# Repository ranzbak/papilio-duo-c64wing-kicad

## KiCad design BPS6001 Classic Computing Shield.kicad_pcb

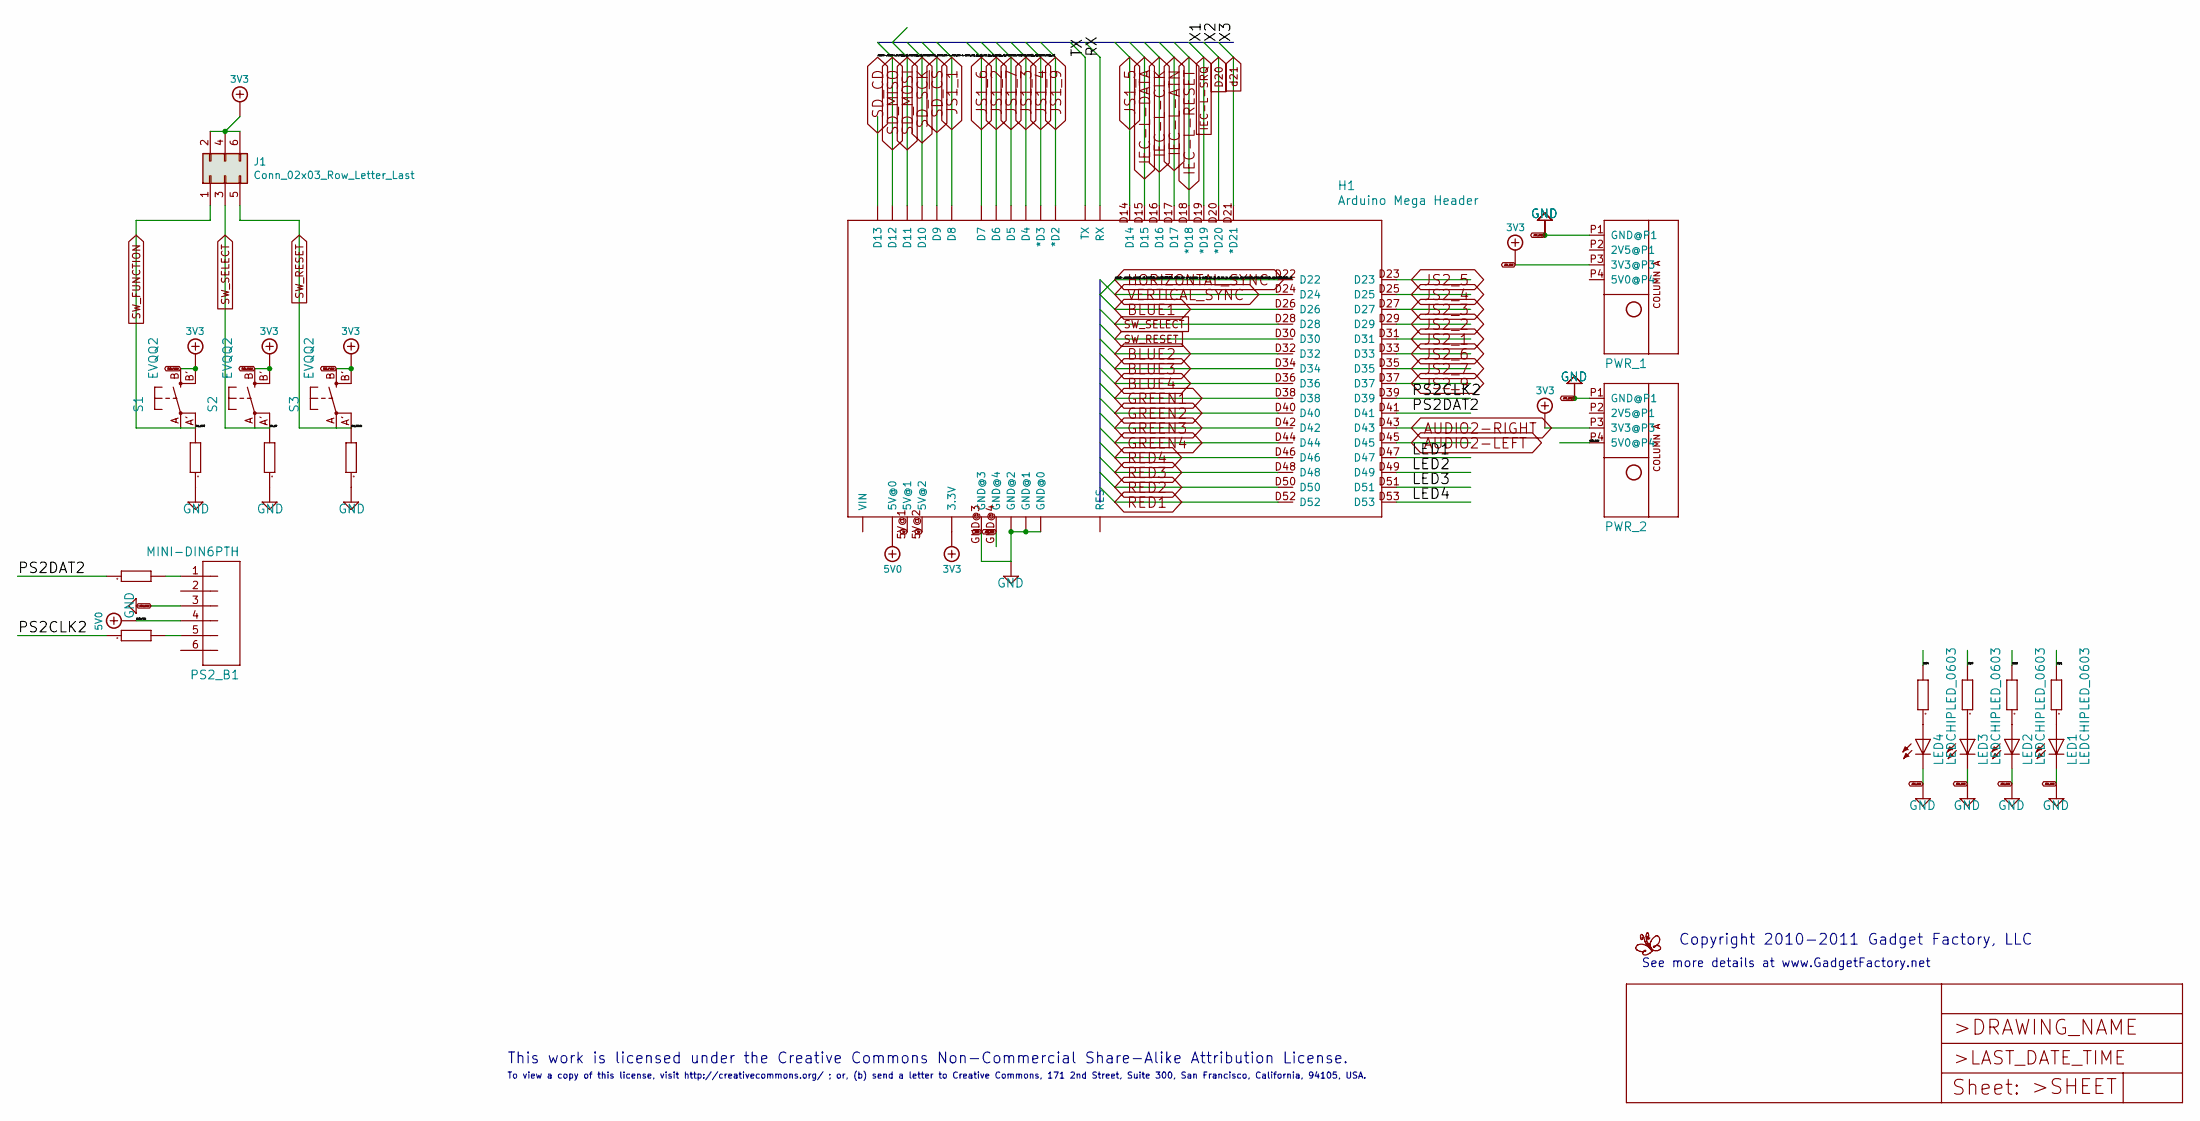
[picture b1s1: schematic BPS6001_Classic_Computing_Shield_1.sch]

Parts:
H1: Arduino Mega Header; AMEGA_SHIELD_NOANALOG; PARTNO Arduino_Mega_Header
J1: Conn_02x03_Row_Letter_Last; PinSocket_2x03_P2.54mm_Vertical
LED1, LED2, LED3, LED4: LEDCHIPLED_0603; CHIPLED_0603; PARTNO LTST-C190GKT
LOGO1: BUTTERFLY_LOGO
PS2_B: MINI-DIN6PTH; MINI-DIN6
PWR_1, PWR_2: POWER_ONLYNOTEXT; POWER_NO_TEXT
R9, R10, R17: 47K; 0603; PARTNO RMCF0603JT47K0
R26, R27, R43, R44, R47, R48: 390; 0603; PARTNO RMCF0603JT390R
S1, S3, S4: EVQQ2; EVQ-Q2; PARTNO PTS525SM10SMTR LFS

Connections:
3V3_PWR6: H1.3.3V, J1.2, J1.4, J1.6, PWR_1.P3 (3V3@P3), PWR_2.P3 (3V3@P3), S1.B (S), S1.B' (S1), S3.B (S), S3.B' (S1); also elsewhere on the board
5V: H1.5V@1, H1.5V@2
5V0: H1.5V@0, PWR_2.P4 (5V0@P4); also elsewhere on the board
/BPS6001 Classic Computing Shield_1/LED1: H1.D47, R26.2
/BPS6001 Classic Computing Shield_1/LED2: H1.D49, R27.2
/BPS6001 Classic Computing Shield_1/LED3: H1.D51, R43.2
/BPS6001 Classic Computing Shield_1/LED4: H1.D53, R44.2
/BPS6001 Classic Computing Shield_1/PS2CLK2: H1.D39, R48.1
/BPS6001 Classic Computing Shield_1/PS2DAT2: H1.D41, R47.1
/BPS6001 Classic Computing Shield_1/RX: H1.RX
/BPS6001 Classic Computing Shield_1/TX: H1.TX
AUDIO2-LEFT: H1.D45; also elsewhere on the board
AUDIO2-RIGHT: H1.D43; also elsewhere on the board
BLUE1: H1.D26; also elsewhere on the board
BLUE2: H1.D32; also elsewhere on the board
BLUE3: H1.D34; also elsewhere on the board
BLUE4: H1.D36; also elsewhere on the board
GND: H1.GND@0, H1.GND@1, H1.GND@2, H1.GND@3, H1.GND@4, LED1.C, LED2.C, LED3.C, LED4.C, PWR_1.P1 (GND@P1), PWR_2.P1 (GND@P1), R9.1, R10.1, R17.1; also elsewhere on the board
GREEN1: H1.D38; also elsewhere on the board
GREEN2: H1.D40; also elsewhere on the board
GREEN3: H1.D42; also elsewhere on the board
GREEN4: H1.D44; also elsewhere on the board
HORIZONTAL_SYNC: H1.D22; also elsewhere on the board
IEC-L-ATN: H1.D17; also elsewhere on the board
IEC-L-CLK: H1.D16; also elsewhere on the board
IEC-L-DATA: H1.D15; also elsewhere on the board
IEC-L-RESET: H1.D18 (*D18); also elsewhere on the board
IEC-L-SRQ: H1.D19 (*D19); also elsewhere on the board
JS1_1: H1.D8; also elsewhere on the board
JS1_2: H1.D6; also elsewhere on the board
JS1_3: H1.D4; also elsewhere on the board
JS1_4: H1.D3 (*D3); also elsewhere on the board
JS1_5: H1.D14; also elsewhere on the board
JS1_6: H1.D7; also elsewhere on the board
JS1_7: H1.D5; also elsewhere on the board
JS1_9: H1.D2 (*D2); also elsewhere on the board
JS2_1: H1.D31; also elsewhere on the board
JS2_2: H1.D29; also elsewhere on the board
JS2_3: H1.D27; also elsewhere on the board
JS2_4: H1.D25; also elsewhere on the board
JS2_5: H1.D23; also elsewhere on the board
JS2_6: H1.D33; also elsewhere on the board
JS2_7: H1.D35; also elsewhere on the board
JS2_9: H1.D37; also elsewhere on the board
unnamed: LED1.A, R26.1
unnamed: LED2.A, R27.1
unnamed: LED3.A, R43.1
unnamed: LED4.A, R44.1
unnamed 63: R47.2; also elsewhere on the board
unnamed 65: R48.2; also elsewhere on the board
RED1: H1.D52; also elsewhere on the board
RED2: H1.D50; also elsewhere on the board
RED3: H1.D48; also elsewhere on the board
RED4: H1.D46; also elsewhere on the board
SD_MISO: H1.D12; also elsewhere on the board
SD_MOSI: H1.D11; also elsewhere on the board
SD_SCK: H1.D10; also elsewhere on the board
SD_~CS: H1.D9; also elsewhere on the board
VERTICAL_SYNC: H1.D24; also elsewhere on the board

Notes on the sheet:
This work is licensed under the Creative Commons Non-Commercial Share-Alike Attribution License.
To view a copy of this license, visit http://creativecommons.org/ ; or, (b) send a letter to Creative Commons, 171 2nd Street, Suite 300, San Francisco, California, 94105, USA.
Copyright 2010-2011 Gadget Factory, LLC
See more details at www.GadgetFactory.net

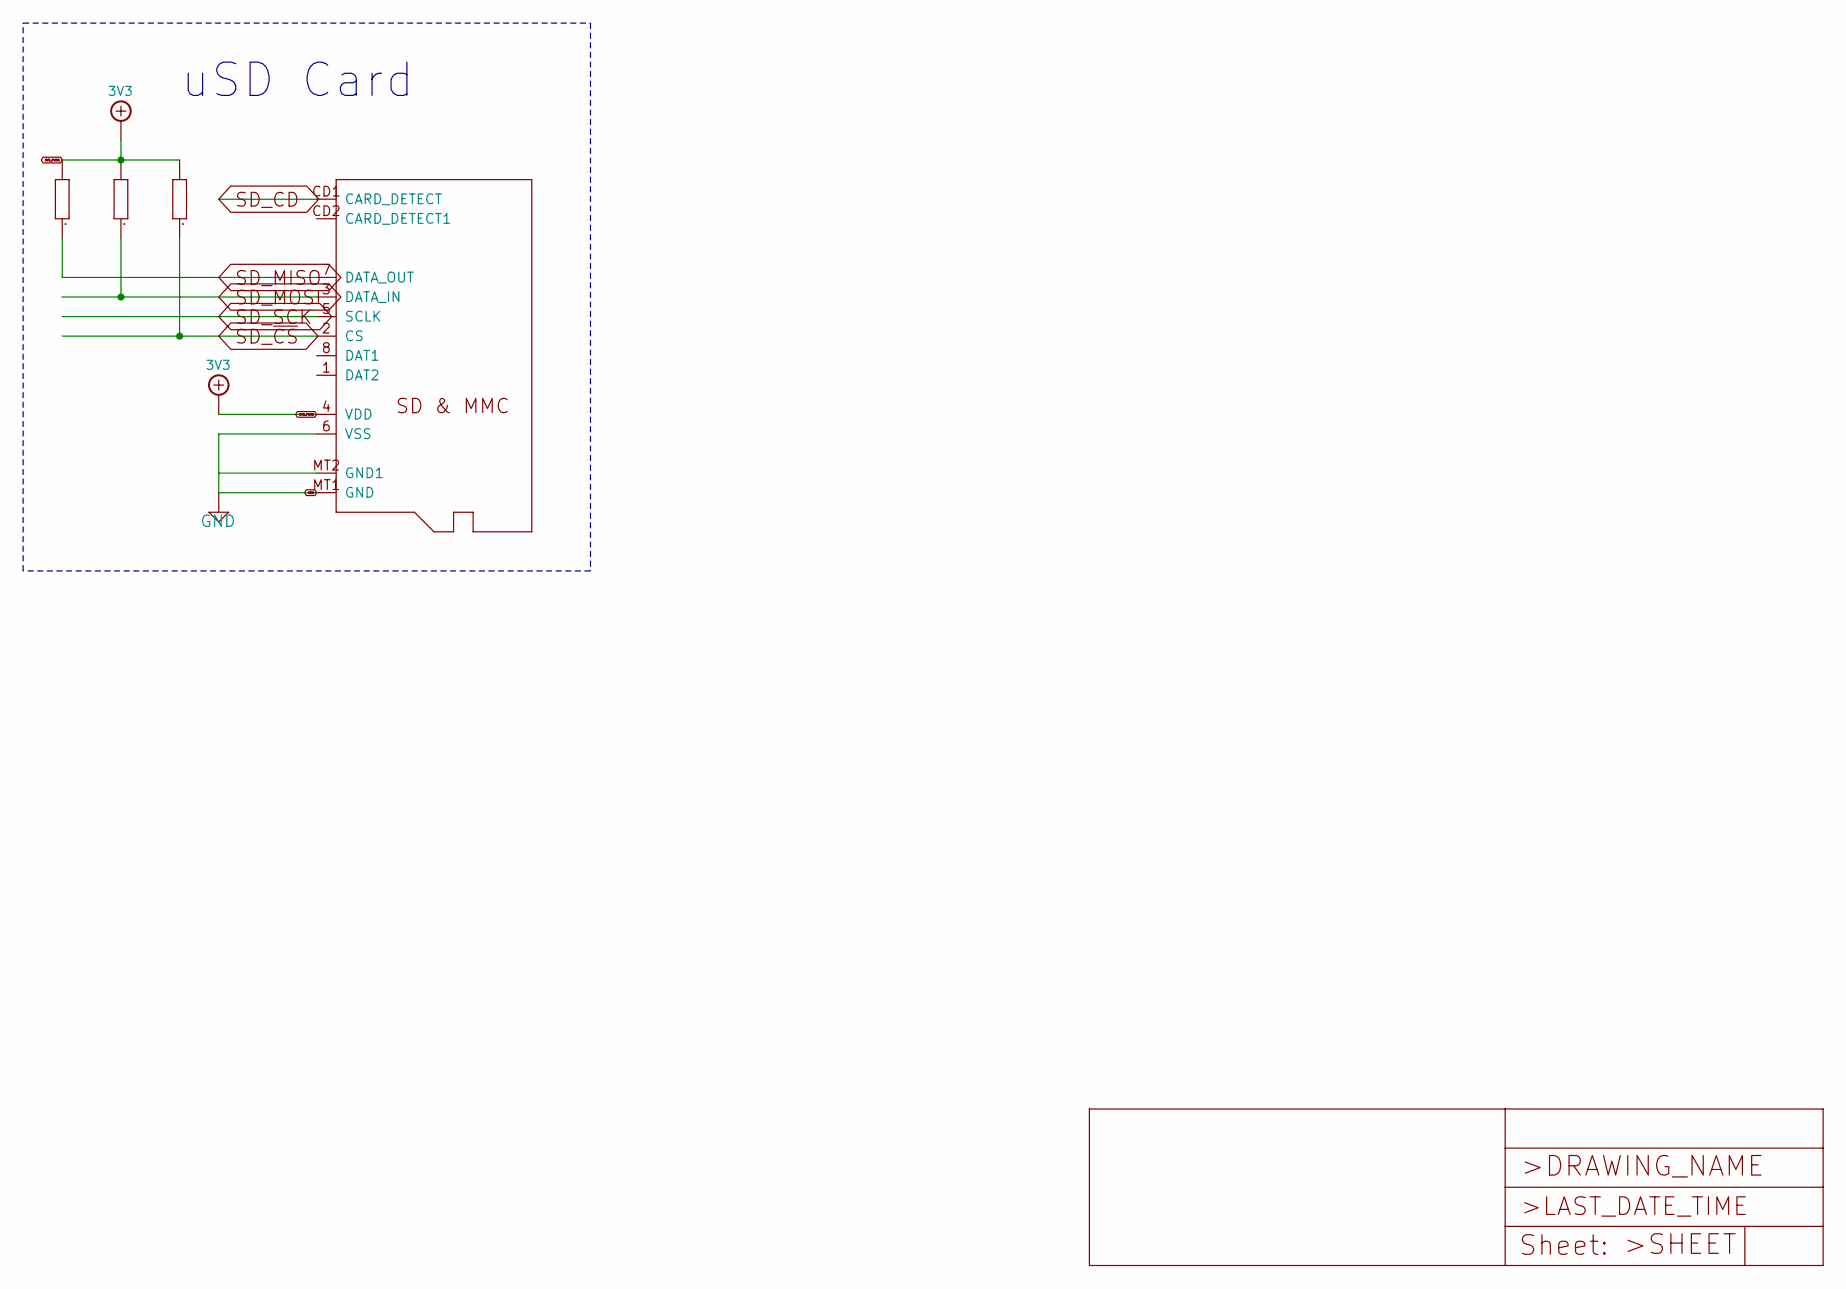
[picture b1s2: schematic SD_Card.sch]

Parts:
R23, R24, R25: 47K; 0603; PARTNO RMCF0603JT47K0
SD1: MICROSD; PARTNO 101-00660-68-6

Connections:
3V3_PWR6: R23.2, R24.2, R25.2, SD1.4 (VDD); also elsewhere on the board
GND: SD1.6 (VSS), SD1.MT1 (GND), SD1.MT2 (GND1); also elsewhere on the board
SD_CD: SD1.CD1 (CARD_DETECT)
SD_MISO: R23.1, SD1.7 (DATA_OUT); also elsewhere on the board
SD_MOSI: R24.1, SD1.3 (DATA_IN); also elsewhere on the board
SD_SCK: SD1.5 (SCLK); also elsewhere on the board
SD_~CS: R25.1, SD1.2 (CS); also elsewhere on the board

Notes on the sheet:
uSD Card

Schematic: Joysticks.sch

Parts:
JS1, JS2: Serial Port; M09HP; PARTNO 10090097-P094VLF
R1, R2, R3, R4, R5, R6, R7, R8, R12, R13, R14, R15, R16, R19, R20, R21: 47K; 0603; PARTNO RMCF0603JT47K0

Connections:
3V3_PWR6: R1.2, R2.2, R3.2, R4.2, R5.2, R6.2, R7.2, R8.2, R12.2, R13.2, R14.2, R15.2, R16.2, R19.2, R20.2, R21.2; also elsewhere on the board
GND: JS1.8, JS2.8; also elsewhere on the board
JS1_1: JS1.1, R1.1; also elsewhere on the board
JS1_2: JS1.2, R3.1; also elsewhere on the board
JS1_3: JS1.3, R5.1; also elsewhere on the board
JS1_4: JS1.4, R6.1; also elsewhere on the board
JS1_5: JS1.5, R8.1; also elsewhere on the board
JS1_6: JS1.6, R2.1; also elsewhere on the board
JS1_7: JS1.7, R4.1; also elsewhere on the board
JS1_9: JS1.9, R7.1; also elsewhere on the board
JS2_1: JS2.1, R16.1; also elsewhere on the board
JS2_2: JS2.2, R15.1; also elsewhere on the board
JS2_3: JS2.3, R14.1; also elsewhere on the board
JS2_4: JS2.4, R13.1; also elsewhere on the board
JS2_5: JS2.5, R12.1; also elsewhere on the board
JS2_6: JS2.6, R19.1; also elsewhere on the board
JS2_7: JS2.7, R20.1; also elsewhere on the board
JS2_9: JS2.9, R21.1; also elsewhere on the board

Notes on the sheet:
This work is licensed under the Creative Commons Non-Commercial Attribution Share-Alike License.
To view a copy of this license, visit http://creativecommons.org/ ; or, (b) send a letter to Creative Commons, 171 2nd Street, Suite 300, San Francisco, California, 94105, USA.
Copyright 2010-2012 Gadget Factory, LLC
See more details at www.GadgetFactory.net

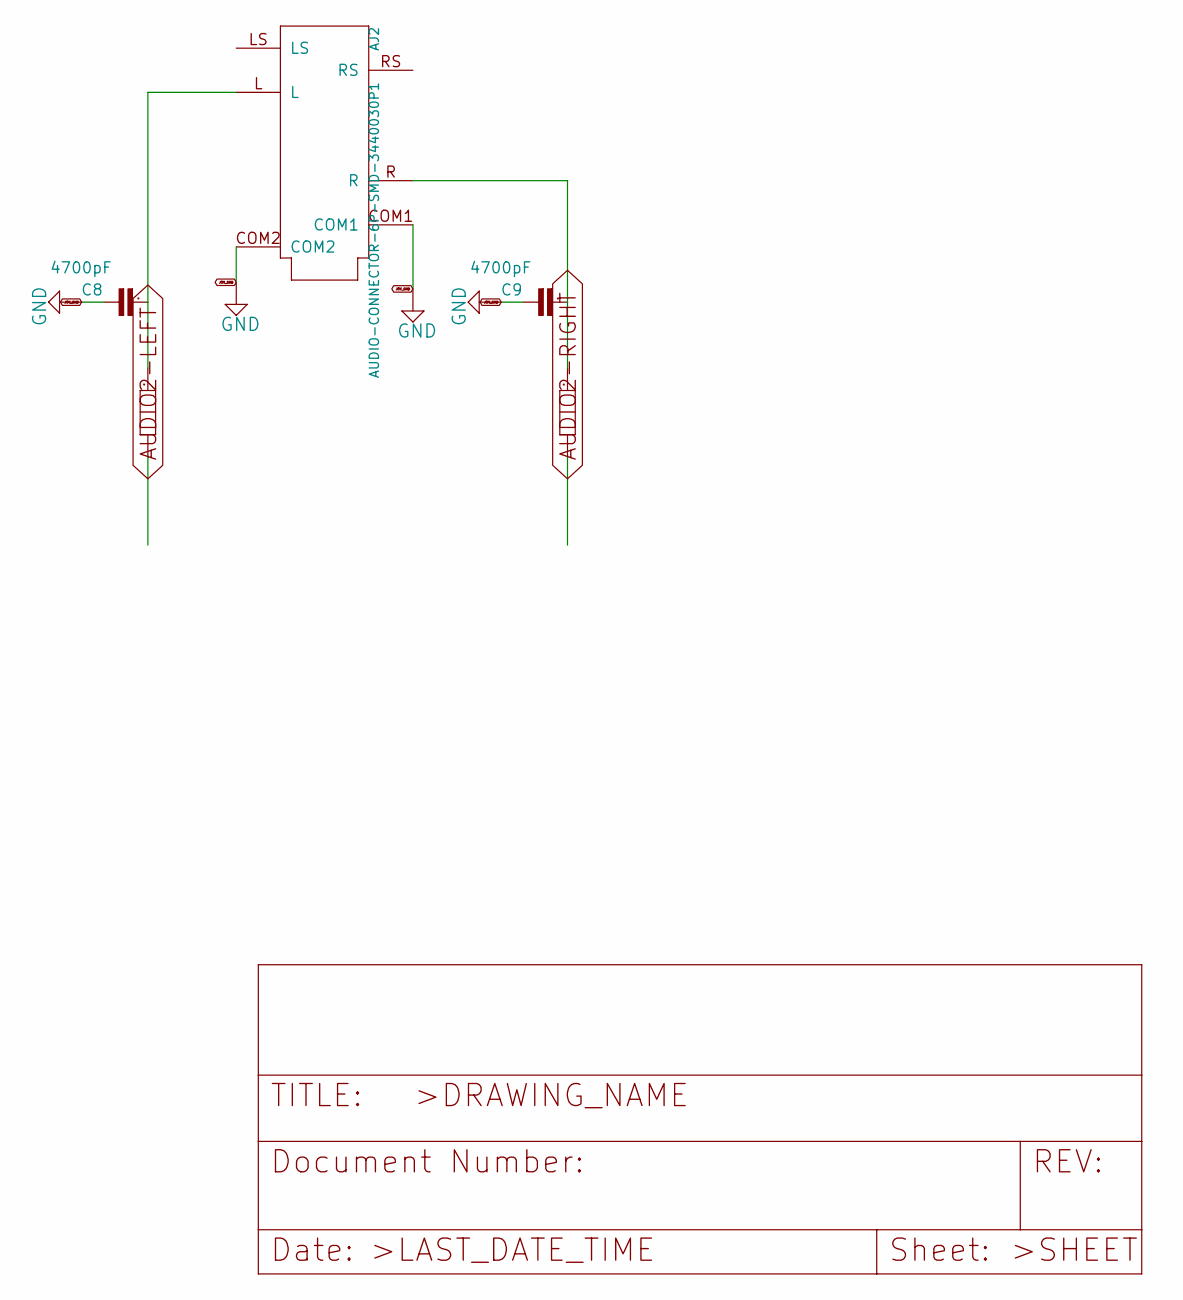
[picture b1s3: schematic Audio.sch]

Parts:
AJ2: AUDIO-CONNECTOR-6P-SMD-3440030P1; 6P-SMD-3.5; PARTNO 3440030P1
C8, C9: 4700pF; 0603; PARTNO C0603C472J5RACTU
R45, R46: 3.3K; 0603; PARTNO RMCF0603JT3K30

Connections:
AUDIO2-LEFT: R45.2; also elsewhere on the board
AUDIO2-RIGHT: R46.2; also elsewhere on the board
GND: AJ2.COM1, AJ2.COM2, C8.2, C9.2; also elsewhere on the board
unnamed: AJ2.L, C8.1, R45.1
unnamed: AJ2.R, C9.1, R46.1

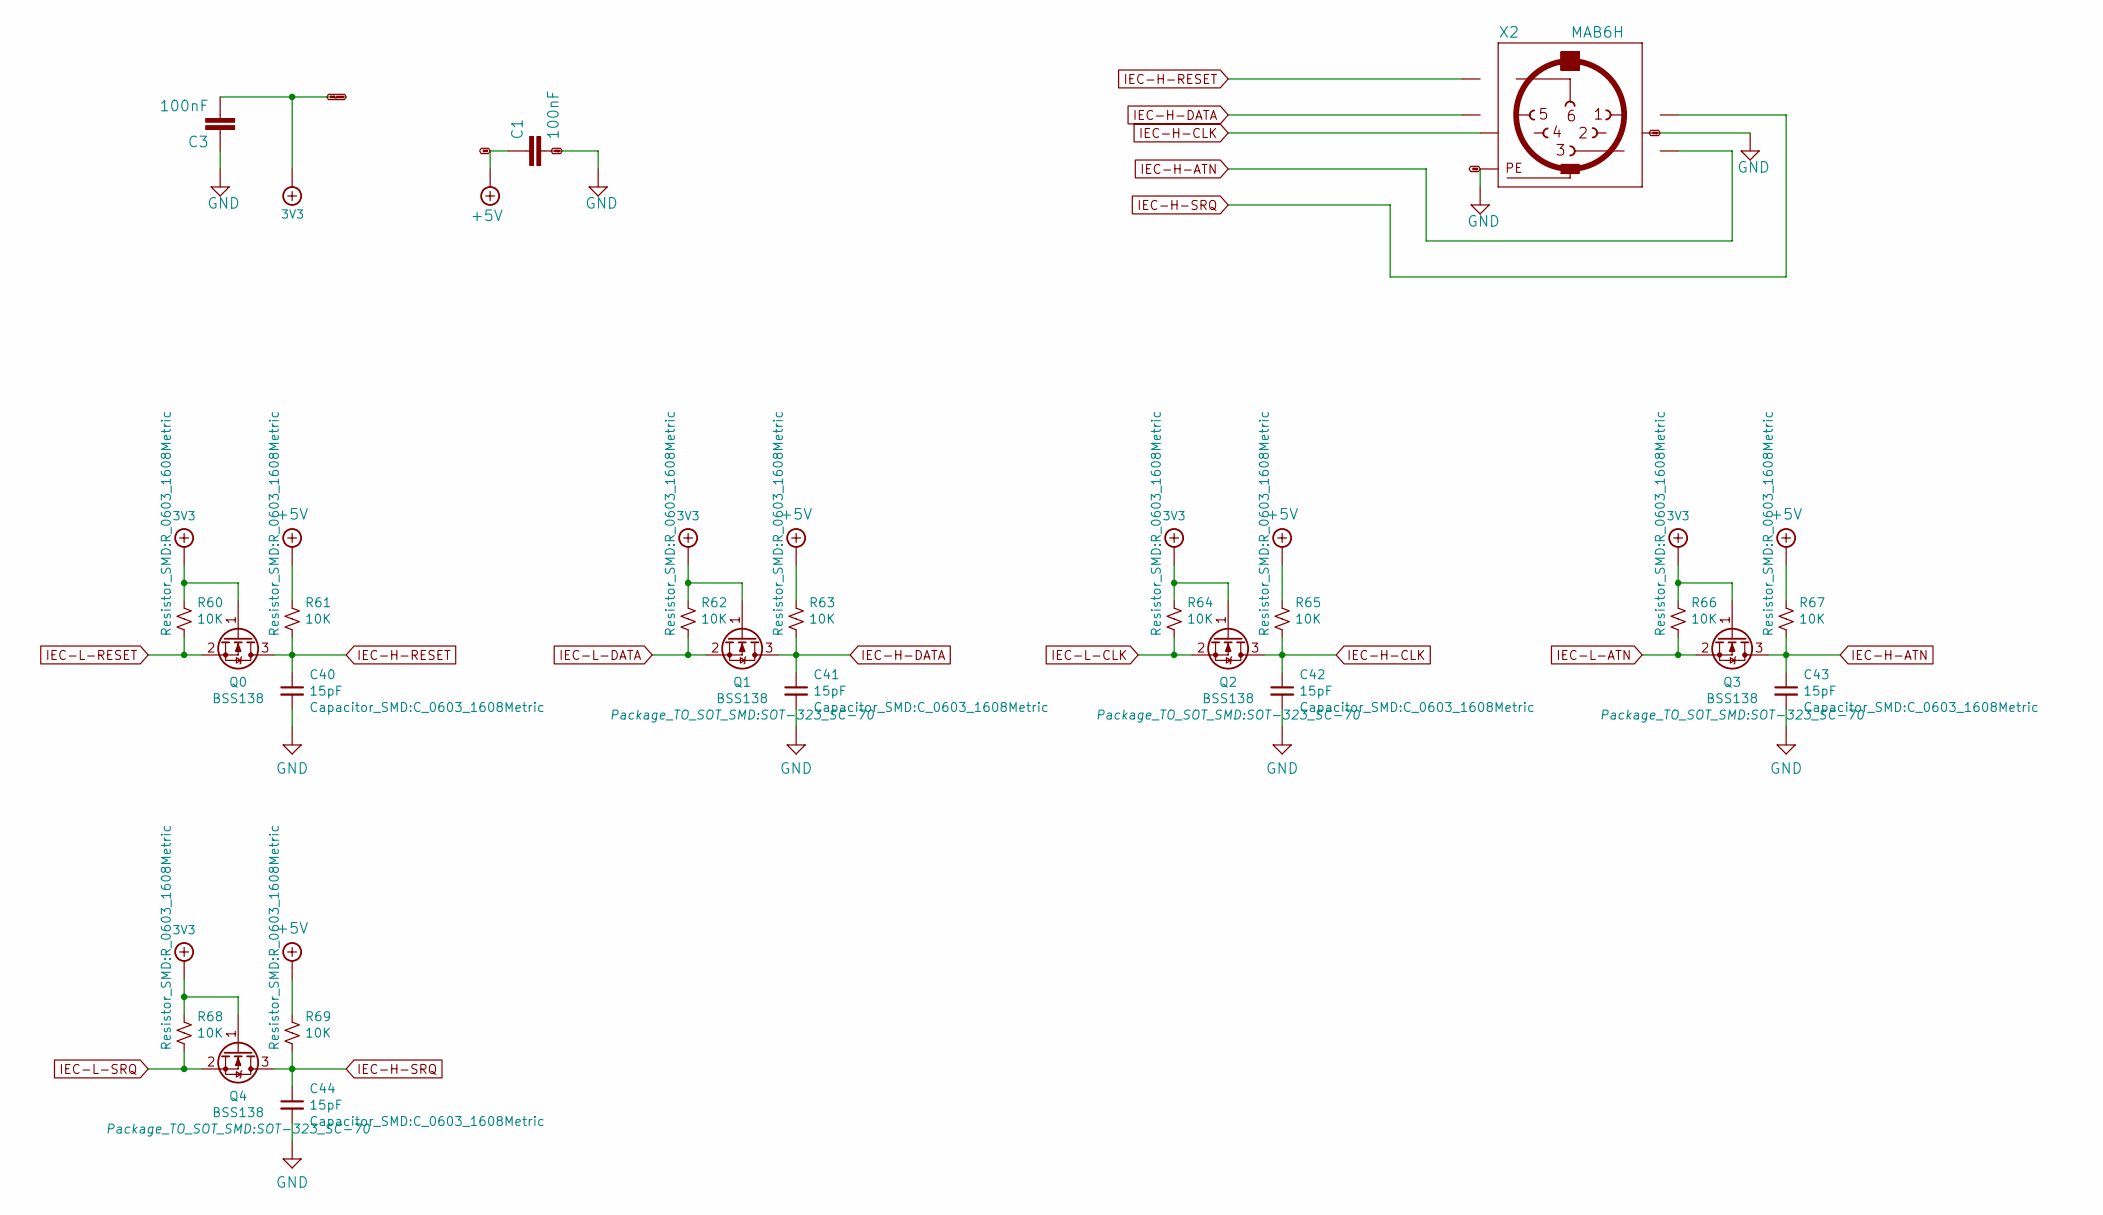
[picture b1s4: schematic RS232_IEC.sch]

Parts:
C1, C3: 100nF; C0603
C40, C41, C42, C43, C44: 15pF; C_0603_1608Metric
Q0, Q1, Q2, Q3, Q4: BSS138; SOT-323_SC-70
R60, R61, R62, R63, R64, R65, R66, R67, R68, R69: 10K; R_0603_1608Metric
X2: MAB6H

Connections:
3V3_PWR6: C3.2, Q0.1 (G), Q1.1 (G), Q2.1 (G), Q3.1 (G), Q4.1 (G), R60.1, R62.1, R64.1, R66.1, R68.1; also elsewhere on the board
5V0: C1.1, R61.1, R63.1, R65.1, R67.1, R69.1; also elsewhere on the board
GND: C1.2, C3.1, C40.2, C41.2, C42.2, C43.2, C44.2, X2.2, X2.PE, X2.PE@ (PE); also elsewhere on the board
IEC-H-ATN: C43.1, Q3.3 (D), R67.2, X2.3
IEC-H-CLK: C42.1, Q2.3 (D), R65.2, X2.4
IEC-H-DATA: C41.1, Q1.3 (D), R63.2, X2.5
IEC-H-RESET: C40.1, Q0.3 (D), R61.2, X2.6
IEC-H-SRQ: C44.1, Q4.3 (D), R69.2, X2.1
IEC-L-ATN: Q3.2 (S), R66.2; also elsewhere on the board
IEC-L-CLK: Q2.2 (S), R64.2; also elsewhere on the board
IEC-L-DATA: Q1.2 (S), R62.2; also elsewhere on the board
IEC-L-RESET: Q0.2 (S), R60.2; also elsewhere on the board
IEC-L-SRQ: Q4.2 (S), R68.2; also elsewhere on the board

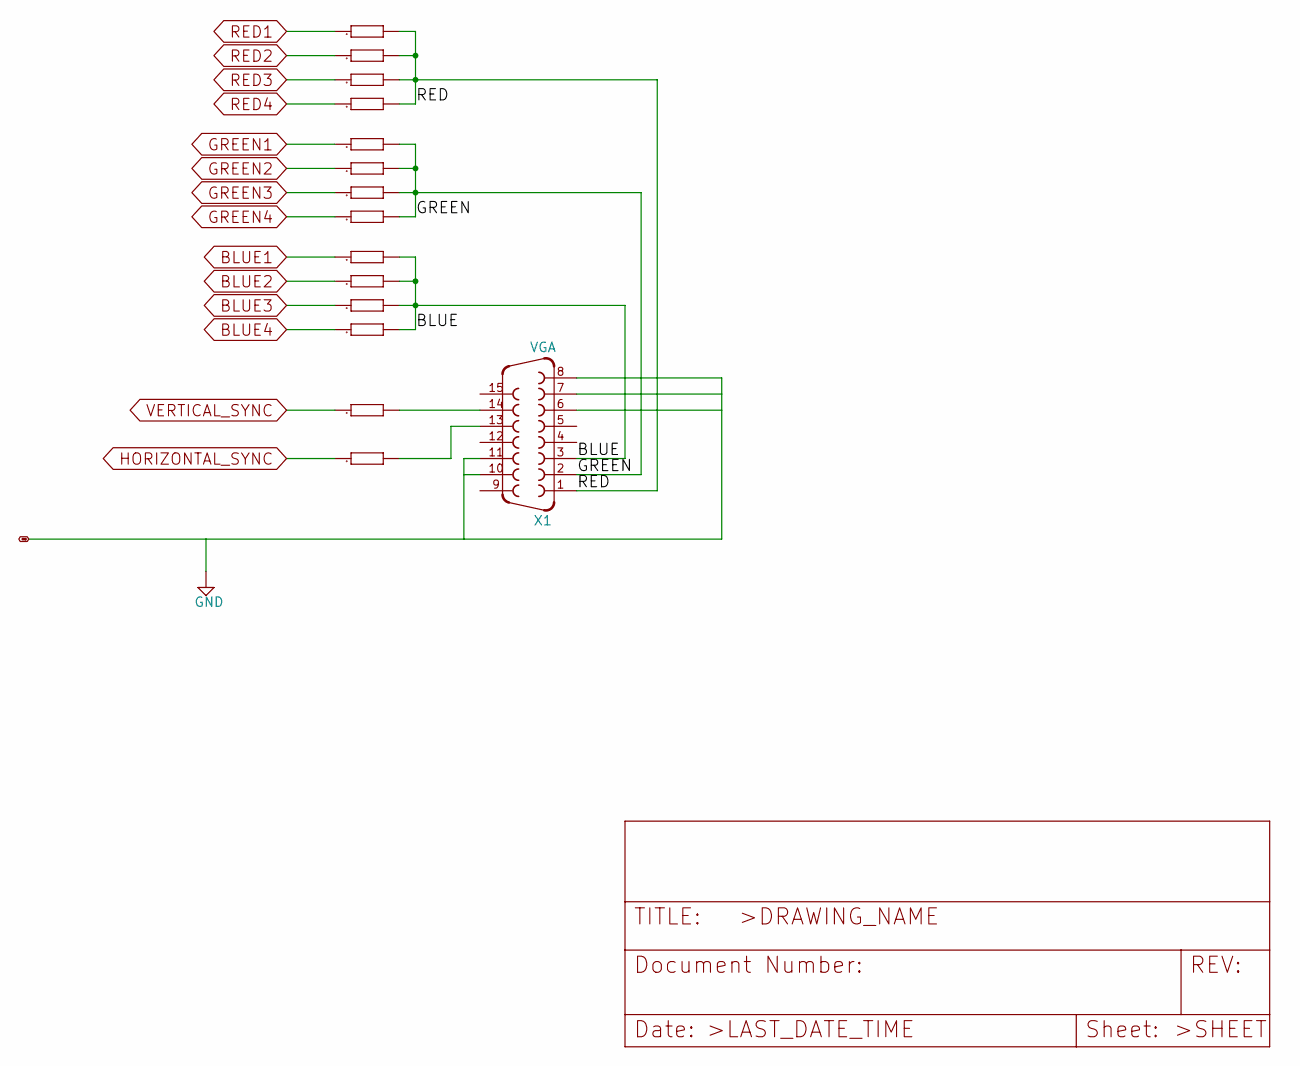
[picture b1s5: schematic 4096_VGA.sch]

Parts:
R29, R30: 82.5; 0603; PARTNO RMCF0603FT82R5
R31, R35, R42: 3.9K; 0603; PARTNO RMCF0603JT3K90
R32, R36, R41: 2K; 0603; PARTNO RMCF0603JT2K00
R33, R37, R40: 1K; 0603; PARTNO RMCF0603JT1K00
R34, R38, R39: 510; 0603; PARTNO RMCF0603JT510R
X1: VGA; HDF15H; PARTNO 1-1734530-1

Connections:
/4096 VGA/BLUE: R31.2, R32.2, R33.2, R34.2, X1.3
/4096 VGA/GREEN: R35.2, R36.2, R37.2, R38.2, X1.2
/4096 VGA/RED: R39.2, R40.2, R41.2, R42.2, X1.1
BLUE1: R31.1; also elsewhere on the board
BLUE2: R32.1; also elsewhere on the board
BLUE3: R33.1; also elsewhere on the board
BLUE4: R34.1; also elsewhere on the board
GND: X1.6, X1.7, X1.8, X1.10, X1.11; also elsewhere on the board
GREEN1: R35.1; also elsewhere on the board
GREEN2: R36.1; also elsewhere on the board
GREEN3: R37.1; also elsewhere on the board
GREEN4: R38.1; also elsewhere on the board
HORIZONTAL_SYNC: R29.1; also elsewhere on the board
unnamed: R29.2, X1.13
unnamed: R30.2, X1.14
RED1: R42.1; also elsewhere on the board
RED2: R41.1; also elsewhere on the board
RED3: R40.1; also elsewhere on the board
RED4: R39.1; also elsewhere on the board
VERTICAL_SYNC: R30.1; also elsewhere on the board

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
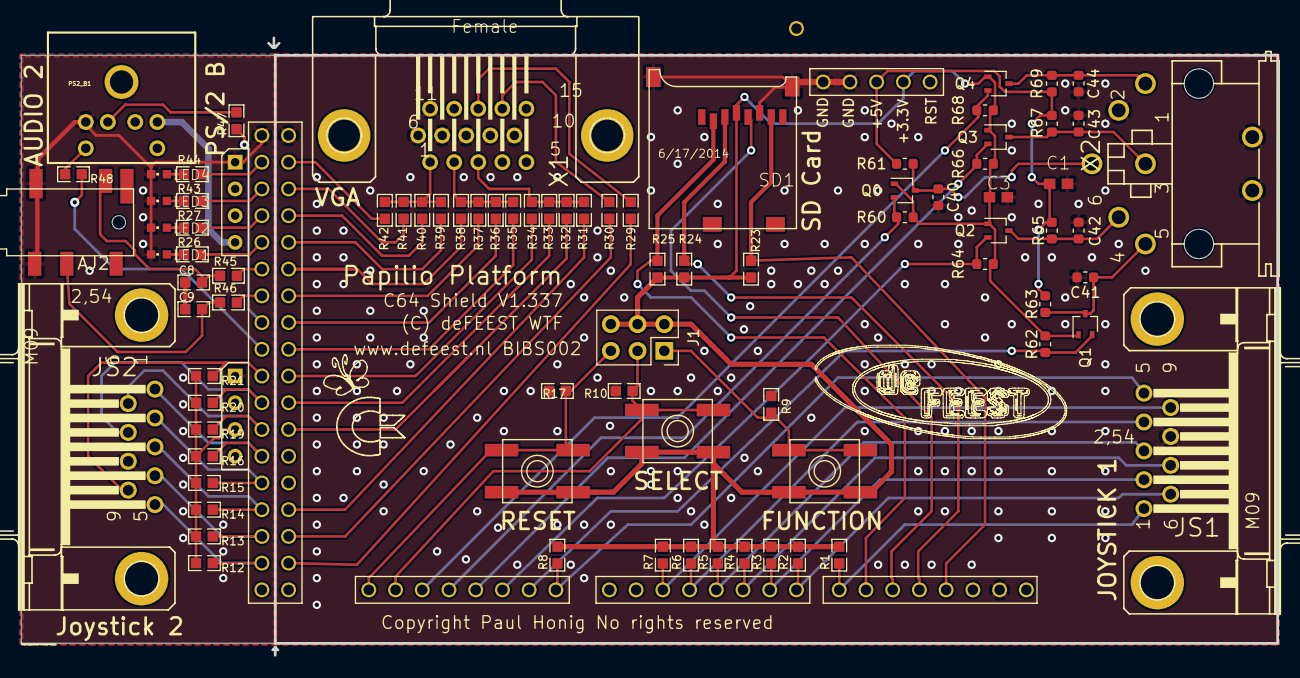
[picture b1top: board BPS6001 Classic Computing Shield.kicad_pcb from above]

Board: 2 copper layers, 119.3 x 58.7 mm, 87 parts (0 on the bottom side), 72 nets.

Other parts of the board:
PS2_B1: MINI-DIN6PTH; MINI-DIN6
S2: EVQQ2; EVQ-Q2

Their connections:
3V3_PWR6: S2.B, S2.B'; also elsewhere on the board
5V0: PS2_B1.4; also elsewhere on the board
GND: PS2_B1.3; also elsewhere on the board
unnamed 63: PS2_B1.1; also elsewhere on the board
unnamed 65: PS2_B1.5; also elsewhere on the board

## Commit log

2019-07-26 First KiCAD conversion.
2019-07-26 Cleanup -bak file.
2019-08-10 Revision 2, needs extra check.
2019-08-17 Moved some vias around to balance the return currents more.

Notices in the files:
BPS6001 Classic Computing Shield.kicad_pcb:
Copyright Paul Honig No rights reserved
